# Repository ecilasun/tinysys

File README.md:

# tinysys

# What is it?

Tinysys started out as a hobby project. It now has two RISC-V cores, and several other facilities listed below, and can happily run most software with minimal tweaks.

Of course, before you ask, it does run DOOM, and with sound and keyboard input! (Lately, it has been running Quake as well.)

# System specifications

- 2x RISC-V based CPUs (architecture: rv32im_zicsr_zifencei_zfinx)
- First core runs the OS kernel and user processes
- Second core is reserved for user processes
- 175MHz bus and CPU clock, semi-pipelined execution
- Vectored or direct interrupt support
- Supports instruction fence and data cache flush/invalidate operations
- Single precision FPU per CPU (no float control CRSs)
- Float and integer GPRs share the same register space (zfinx extension)
- 32 GRPs x 32 bits
- 4096 CSRs x 32 bits (some registers reserved for CPU and some are immutable)
- All CPUs have access to each-other's CSR register files via memory mapped addresses
- Integer multiply / divide units per CPU
- Software, hardware and timer interrupts per CSR per core
- 16Kbytes of direct mapped instruction cache (256 lines x 64 bytes)
- 32Kbytes of direct mapped data cache (512 lines x 64 bytes)
- 128 bit AXI4 bus with 32 bit address line
- Memory arbiter for on-board device system memory access (round-robin)
- Memory mapped external hardware (audio / video etc)
- HDMI 1.4b compatible video and audio output via external chip (12 bits per pixel, 16bps stereo 44/22/11KHz for audio, RGB or paletted modes)
- SDCard for file I/O
- 4 debug LEDs (also shared by OS as indicators)
- Custom preemptive multitasking OS, with file I/O and basic memory allocator via syscalls
- Optionally, a rom.bin image can be loaded from SDCard to replace the OS in ROM
- ESP32S3 on board for I/O handling (UART serial connected directly for CLI and other future connectivity, running at 460800 baud)
- Future revisions will use USB-OTG on the ESP32S3 module to allow for mass storage access to the device
- 16Kbytes mailbox memory for task scheduler + general purpose use (uncached)
- 16Kbytes of scratchpad memory for inter-processor communications or temporary data storage (uncached)
- Horizontal blanking interrupts to synchronize CPU with VPU for video effects or interrupt driven vsync page flip

# Overview of the processing units

## CPU
Based on 32 bit RISC-V ISA. Implements base integer instruction set, required cache operations (I$ and D$) and a large CSR file.
The core currently has an average instruction retirement rate of ~6 CPI (clocks per instruction) and runs at 175MHz, which
is also the speed of the AXI4 bus, where all peripherals and memory reside.

### Fetch/Decode/IRQ
This unit reads an instruction at PC, decodes it and outputs it (together with its PC) to instruction output FIFO (IFIFO). If it's an interrupt entry/exit or some other special instruction (for instance I$ flush) then it is handled entirely within the fetch unit. This unit is also responsible for inserting pre/post interrupt code from an internal ROM at interrupt or exception time. Conditional branches will place fetch unit into an idle state, where it will wait for the execute unit to resolve the target branch address. This means there's no branch prediction on the CPU just yet.

### Execute/Load/Store
This unit will read an instruction from the IFIFO if available, load registers with values, execute (ALU/BLU/CSR/SYS) and decide on new branch target if there's a branch involved. After deciding on the branch address, fetch unit is notified so it can resume instruction fetches. Where possible, load or store operations will attempt to overlap with fetch and execution.

## VPU
Video processing unit. Handles scan-out of various video sizes (320x240 and 640x480) and bit depths (8bpp index color or 16bpp RGB color). It contains a scanline cache which is populated via burst reads from system memory, from which either a scan-doubled or single line is output to the display, based on video mode height. The device allows for mid-frame change of resolution via hblank interrupts.

## APU
Audio processing unit. Handles RAW audio outputs, and also manages 44/22/11KHz stereo playback and double-buffer handling of RAW audio.

# Overview of the bus

## AXI4 bus
The AXI4 bus, running at 175MHz, connects all of the processing units to memory or devices. In the case of memory, access is cached per perhipheral as needed. Memory mapped device access is always uncached.

# Contributors

```
Martin Hedlund

  tbm_vsnprintf() and tbm_printf() functions

Wade Brainerd

  fcvtswu4sat instruction
```

# Custom instructions

## Convert from float to 4 bit integer, saturated (FCVTSWU5SAT)

This instuction has been contributed by Wade Brainerd. It's very useful in converting floating point values to device specific 4 bit color values.

The following python script helps encode a hex representation of this instruction, for convenience:

```
op = 0b1010011		# OP-FP (floating point operation)
rd = 0b01010		# destination register - a0 in this sample (a0 == x10)
rs1 = 0b01011		# source register - a1 in this sample (a1 == x11)
funct7 = 0b1100001	# funct5 F7_FCVTSWU5SAT - this is our new sub-instruction
inst = op | (rd << 7) | (rs1 << 15) | (funct7 << 25)

print(f"{inst:x}")
```

You can then use it in code as follows:

```
inline uint32_t ftoui4sat(float value)
{
  uint32_t retval;
  asm (
    "mv a1, %1;"
    ".insn 0xc2058553;" // fcvtswu4sat a0, a1 // note A0==cpu.x10, A1==cpu.x11
    "mv %0, a0; "
    : "=r" (retval)
    : "r" (value)
    : "a0", "a1"
  );
  return retval;
}
```

P.S. For the future we might be able to do this natively on a RISC-V or propose an extension for arbitrary saturation for custom formats.

# Software

Please see [README.md](./software/README.md) for details on software samples, ROM and prerequisites for building ELF files.

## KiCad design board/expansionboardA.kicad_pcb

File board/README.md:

# expansionboardA

This repository contains KiCAD 7 project files for an expansion module built for QMTECH A7 200T core board.
Required libraries (models and symbols) are included with the project.

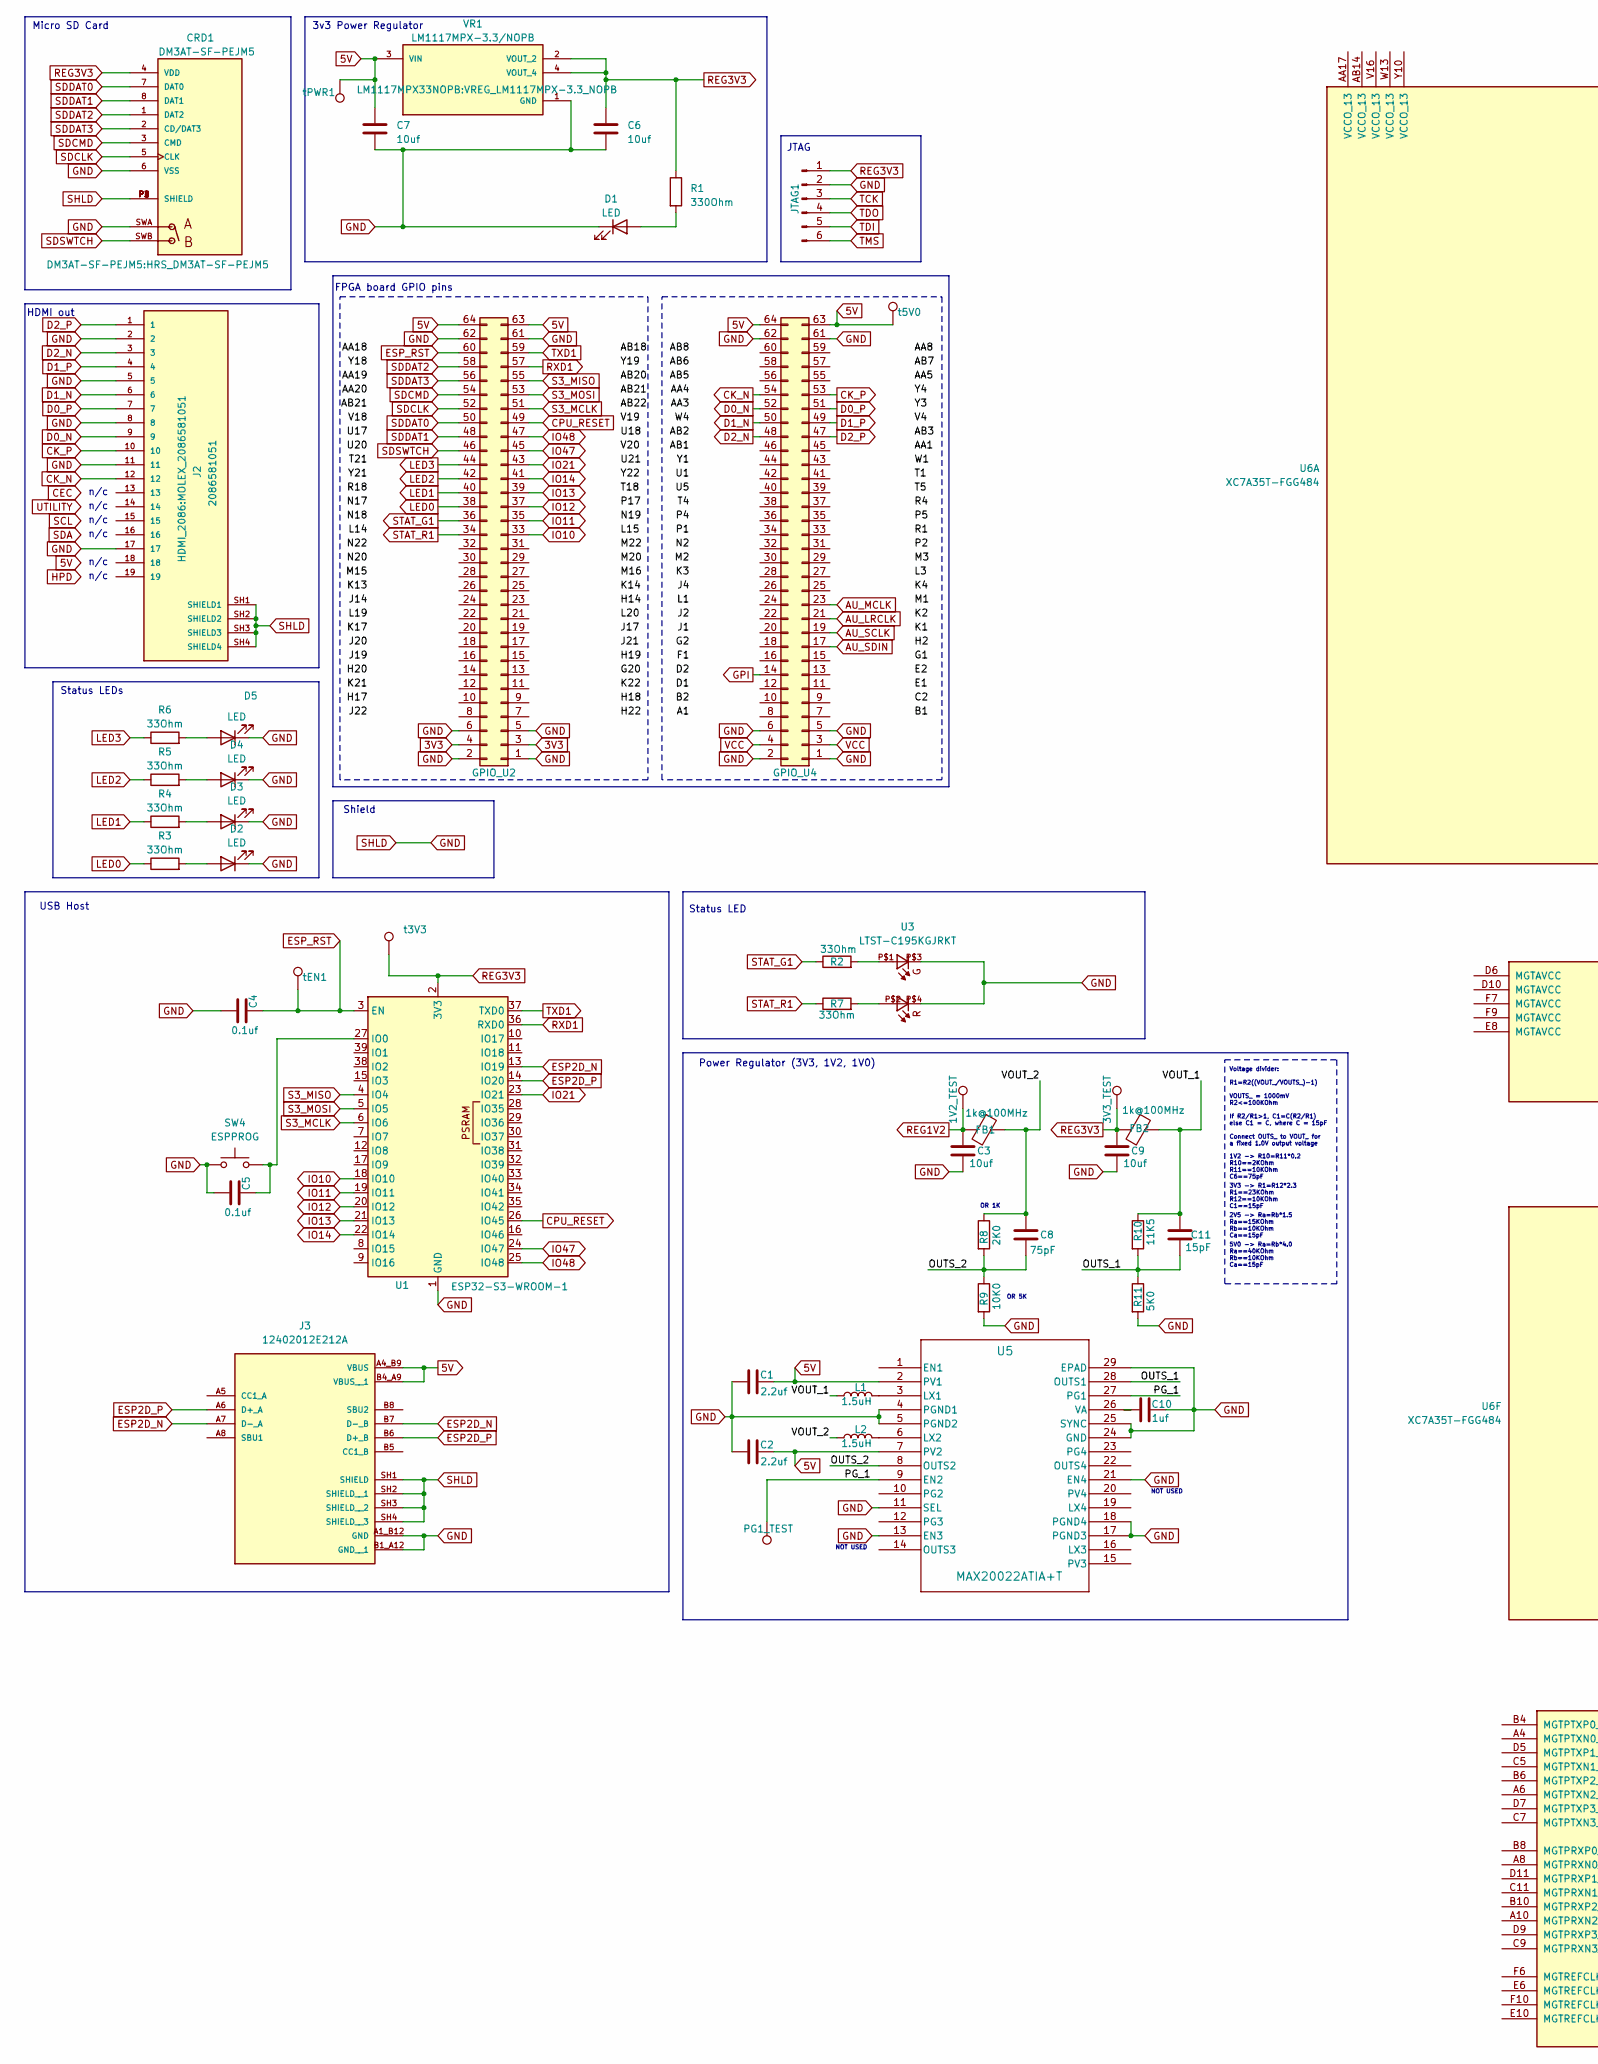
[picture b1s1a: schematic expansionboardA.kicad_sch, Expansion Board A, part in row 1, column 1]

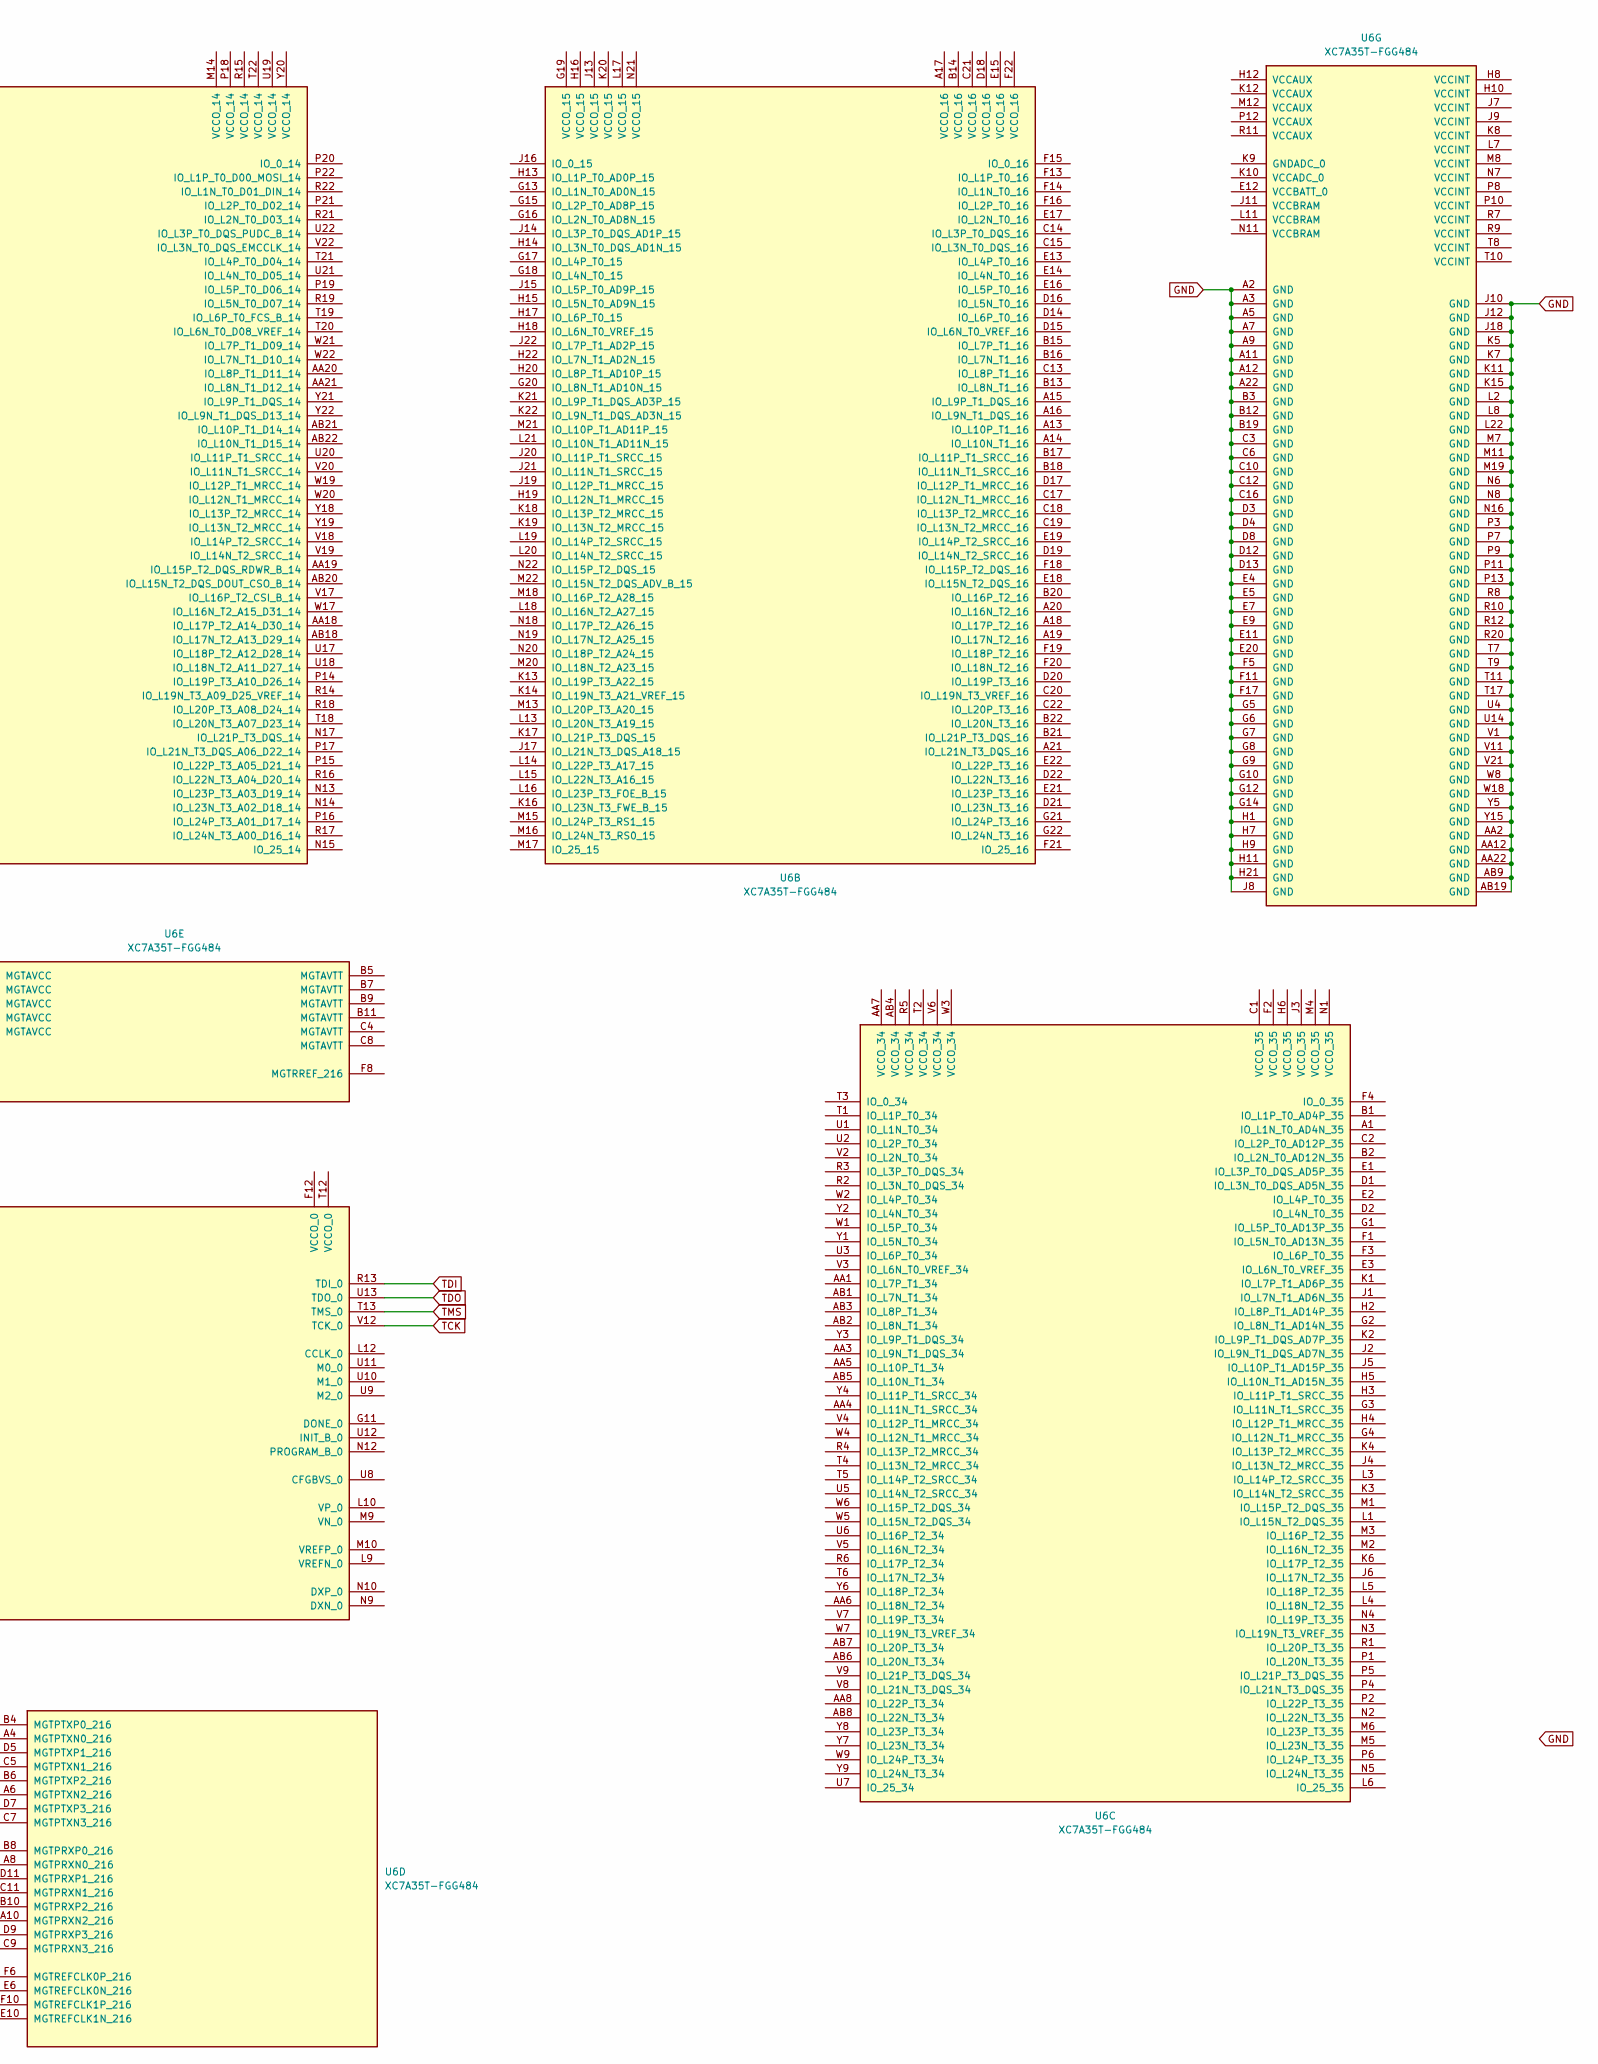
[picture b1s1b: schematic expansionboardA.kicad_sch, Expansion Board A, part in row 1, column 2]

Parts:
C1, C2: 2.2uf; C_0603_1608Metric_Pad1.08x0.95mm_HandSolder
C3, C9: 10uf; C_0603_1608Metric_Pad1.08x0.95mm_HandSolder
C4, C5: 0.1uf; C_0603_1608Metric_Pad1.08x0.95mm_HandSolder
C6, C7: 10uf; C_0805_2012Metric_Pad1.18x1.45mm_HandSolder
C8: 75pF; C_0603_1608Metric_Pad1.08x0.95mm_HandSolder
C10: 1uf; C_0603_1608Metric_Pad1.08x0.95mm_HandSolder
C11: 15pF; C_0603_1608Metric_Pad1.08x0.95mm_HandSolder
CRD1: DM3AT-SF-PEJM5; HRS_DM3AT-SF-PEJM5
D1, D2, D3, D4, D5: LED; LED_1206_3216Metric_Pad1.42x1.75mm_HandSolder
FB1, FB2: 1k@100MHz; R_0805_2012Metric_Pad1.20x1.40mm_HandSolder
J2: 2086581051; MOLEX_2086581051; PARTREV A
J3: 12402012E212A; AMPHENOL_12402012E212A; PARTREV 4
JTAG1: Conn_01x06_Pin; PinHeader_1x06_P2.54mm_Vertical
L1, L2: 1.5uH; L_0805_2012Metric
R1: 330Ohm; R_0603_1608Metric_Pad0.98x0.95mm_HandSolder
R2, R3, R4, R5, R6, R7: 33Ohm; R_0603_1608Metric_Pad0.98x0.95mm_HandSolder
R8: 2K0; R_0603_1608Metric_Pad0.98x0.95mm_HandSolder
R9: 10K0; R_0603_1608Metric_Pad0.98x0.95mm_HandSolder
R10: 11K5; R_0603_1608Metric_Pad0.98x0.95mm_HandSolder
R11: 5K0; R_0603_1608Metric_Pad0.98x0.95mm_HandSolder
SW4: ESPPROG; SW_Tactile_SPST_NO_Straight_CK_PTS636Sx25SMTRLFS
U1: ESP32-S3-WROOM-1
U2: GPIO_U2; PinSocket_2x32_P2.54mm_Vertical
U3: LTST-C195KGJRKT; LTST-BILED-15X16
U4: GPIO_U4; PinSocket_2x32_P2.54mm_Vertical
U5: MAX20022ATIA+T; 21-0140_T2855&plus_5_MXM-M
U6: XC7A35T-FGG484; Xilinx_FGG484
VR1: LM1117MPX-3.3/NOPB; VREG_LM1117MPX-3.3_NOPB; PARTREV O
t1V1: 1V2_TEST; TestPoint_Pad_1.0x1.0mm
t3V1: 3V3_TEST; TestPoint_Pad_1.0x1.0mm
t3V3, t5V0: TestPoint; TestPoint_Pad_D1.0mm
tEN1: TestPoint; TestPoint_Pad_D1.0mm
tPG1: PG1_TEST; TestPoint_Pad_1.0x1.0mm
tPWR1: TestPoint; TestPoint_Pad_D1.0mm

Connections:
3V3: U2.3, U2.4
5V: C1.2, C2.2, C7.1, J3.A4_B9 (VBUS), J3.B4_A9 (VBUS__1), U2.63, U2.64, U4.63, U4.64, U5.2 (PV1), U5.7 (PV2), VR1.3 (VIN), t5V0.1, tPWR1.1
/OUTS_1: C11.2, R10.2, R11.1, U5.28 (OUTS1)
/OUTS_2: C8.2, R8.2, R9.1, U5.8 (OUTS2)
/PG_1: U5.9 (EN2), U5.27 (PG1), tPG1.1
/VOUT_1: C11.1, FB2.1, L1.1, R10.1
/VOUT_2: C8.1, FB1.1, L2.1, R8.1
AU_LRCLK: U4.21
AU_MCLK: U4.23
AU_SCLK: U4.19
AU_SDIN: U4.17
CK_N: J2.12, U4.54
CK_P: J2.10, U4.53
CPU_RESET: U1.26 (IO45), U2.49
D0_N: J2.9, U4.52
D0_P: J2.7, U4.51
D1_N: J2.6, U4.50
D1_P: J2.4, U4.49
D2_N: J2.3, U4.48
D2_P: J2.1, U4.47
ESP2D_N: J3.A7 (D-_A), J3.B7 (D-_B), U1.13 (IO19)
ESP2D_P: J3.A6 (D+_A), J3.B6 (D+_B), U1.14 (IO20)
ESP_RST: C4.1, U1.3 (EN), U2.60, tEN1.1
GND: C1.1, C2.1, C3.2, C4.2, C5.2, C6.2, C7.2, C9.2, C10.2, CRD1.6 (VSS), CRD1.P1 (SHIELD), CRD1.P2 (SHIELD), CRD1.P3 (SHIELD), CRD1.P4 (SHIELD), CRD1.SWA, D1.1 (K), D2.1 (K), D3.1 (K), D4.1 (K), D5.1 (K), J2.2, J2.5, J2.8, J2.11, J2.17, J2.SH1 (SHIELD1), J2.SH2 (SHIELD2), J2.SH3 (SHIELD3), J2.SH4 (SHIELD4), J3.A1_B12 (GND), J3.B1_A12 (GND__1), J3.SH1 (SHIELD), J3.SH2 (SHIELD__1), J3.SH3 (SHIELD__2), J3.SH4 (SHIELD__3), JTAG1.2, R9.2, R11.2, SW4.1, U1.1 (GND), U1.40 (GND), U1.41 (GND), U2.1, U2.2, U2.5, U2.6, U2.61, U2.62, U3.P$3, U3.P$4, U4.1, U4.2, U4.5, U4.6, U4.61, U4.62, U5.4 (PGND1), U5.5 (PGND2), U5.11 (SEL), U5.13 (EN3), U5.17 (PGND3), U5.18 (PGND4), U5.21 (EN4), U5.24 (GND), U5.25 (SYNC), U5.29 (EPAD), U6.A2 (GND), U6.A3 (GND), U6.A5 (GND), U6.A7 (GND), U6.A9 (GND), U6.A11 (GND), U6.A12 (GND), U6.A22 (GND), U6.AA2 (GND), U6.AA12 (GND), U6.AA22 (GND), U6.AB9 (GND), U6.AB19 (GND), U6.B3 (GND), U6.B12 (GND), U6.B19 (GND), U6.C3 (GND), U6.C6 (GND), U6.C10 (GND), U6.C12 (GND), U6.C16 (GND), U6.D3 (GND), U6.D4 (GND), U6.D8 (GND), U6.D12 (GND), U6.D13 (GND), U6.E4 (GND), U6.E5 (GND), U6.E7 (GND), U6.E9 (GND), U6.E11 (GND), U6.E20 (GND), U6.F5 (GND), U6.F11 (GND), U6.F17 (GND), U6.G5 (GND), U6.G6 (GND), U6.G7 (GND), U6.G8 (GND), U6.G9 (GND), U6.G10 (GND), U6.G12 (GND), U6.G14 (GND), U6.H1 (GND), U6.H7 (GND), U6.H9 (GND), U6.H11 (GND), U6.H21 (GND), U6.J8 (GND), U6.J10 (GND), U6.J12 (GND), U6.J18 (GND), U6.K5 (GND), U6.K7 (GND), U6.K11 (GND), U6.K15 (GND), U6.L2 (GND), U6.L8 (GND)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
GPI: U4.14
IO10: U1.18 (IO10), U2.33
IO11: U1.19 (IO11), U2.35
IO12: U1.20 (IO12), U2.37
IO13: U1.21 (IO13), U2.39
IO14: U1.22 (IO14), U2.41
IO21: U1.23 (IO21), U2.43
IO47: U1.24 (IO47), U2.45
IO48: U1.25 (IO48), U2.47
LED0: R3.1, U2.38
LED1: R4.1, U2.40
LED2: R5.1, U2.42
LED3: R6.1, U2.44
unnamed: D1.2 (A), R1.2
unnamed: D2.2 (A), R3.2
unnamed: D3.2 (A), R4.2
unnamed: D4.2 (A), R5.2
unnamed: D5.2 (A), R6.2
unnamed: R2.2, U3.P$1
unnamed: R7.2, U3.P$2
unnamed: C5.1, SW4.2, U1.27 (IO0)
unnamed: L1.2, U5.3 (LX1)
unnamed: L2.2, U5.6 (LX2)
unnamed: C10.1, U5.26 (VA)
REG1V2: C3.1, FB1.2, t1V1.1
REG3V3: C6.1, C9.1, CRD1.4 (VDD), FB2.2, JTAG1.1, R1.1, U1.2 (3V3), VR1.2 (VOUT_2), VR1.4 (VOUT_4), t3V1.1, t3V3.1
RXD1: U1.36 (RXD0), U2.57
S3_MCLK: U1.6 (IO6), U2.51
S3_MISO: U1.4 (IO4), U2.55
S3_MOSI: U1.5 (IO5), U2.53
SDCLK: CRD1.5 (CLK), U2.52
SDCMD: CRD1.3 (CMD), U2.54
SDDAT0: CRD1.7 (DAT0), U2.50
SDDAT1: CRD1.8 (DAT1), U2.48
SDDAT2: CRD1.1 (DAT2), U2.58
SDDAT3: CRD1.2 (CD/DAT3), U2.56
SDSWTCH: CRD1.SWB, U2.46
STAT_G1: R2.1, U2.36
STAT_R1: R7.1, U2.34
TCK: JTAG1.3, U6.V12 (TCK_0)
TDI: JTAG1.5, U6.R13 (TDI_0)
TDO: JTAG1.4, U6.U13 (TDO_0)
TMS: JTAG1.6, U6.T13 (TMS_0)
TXD1: U1.37 (TXD0), U2.59
VCC: U4.3, U4.4

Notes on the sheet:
NOT USED
OR 1K
2V5 -> Ra=Rb*1.5 Ra==15KOhm Rb==10KOhm Ca==15pF
n/c
FPGA board GPIO pins
5V0 -> Ra=Rb*4.0 Ra==40KOhm Rb==10KOhm Ca==15pF
Micro SD Card
JTAG
Status LED
Power Regulator (3V3, 1V2, 1V0)
Status LEDs
USB Host
Shield
Voltage divider: R1=R2((VOUT_/VOUTS_)−1) VOUTS_ = 1000mV R2<=100KOhm If R2/R1>1, C1=C(R2/R1) else C1 = C, where C = 15pF Connect OUTS_ to VOUT_ for a fixed 1.0V output voltage
1V2 -> R10=R11*0.2 R10==2KOhm R11==10KOhm C6==75pF
3v3 Power Regulator
HDMI out
3V3 -> R1=R12*2.3 R1==23KOhm R12==10KOhm C1==15pF
OR 5K

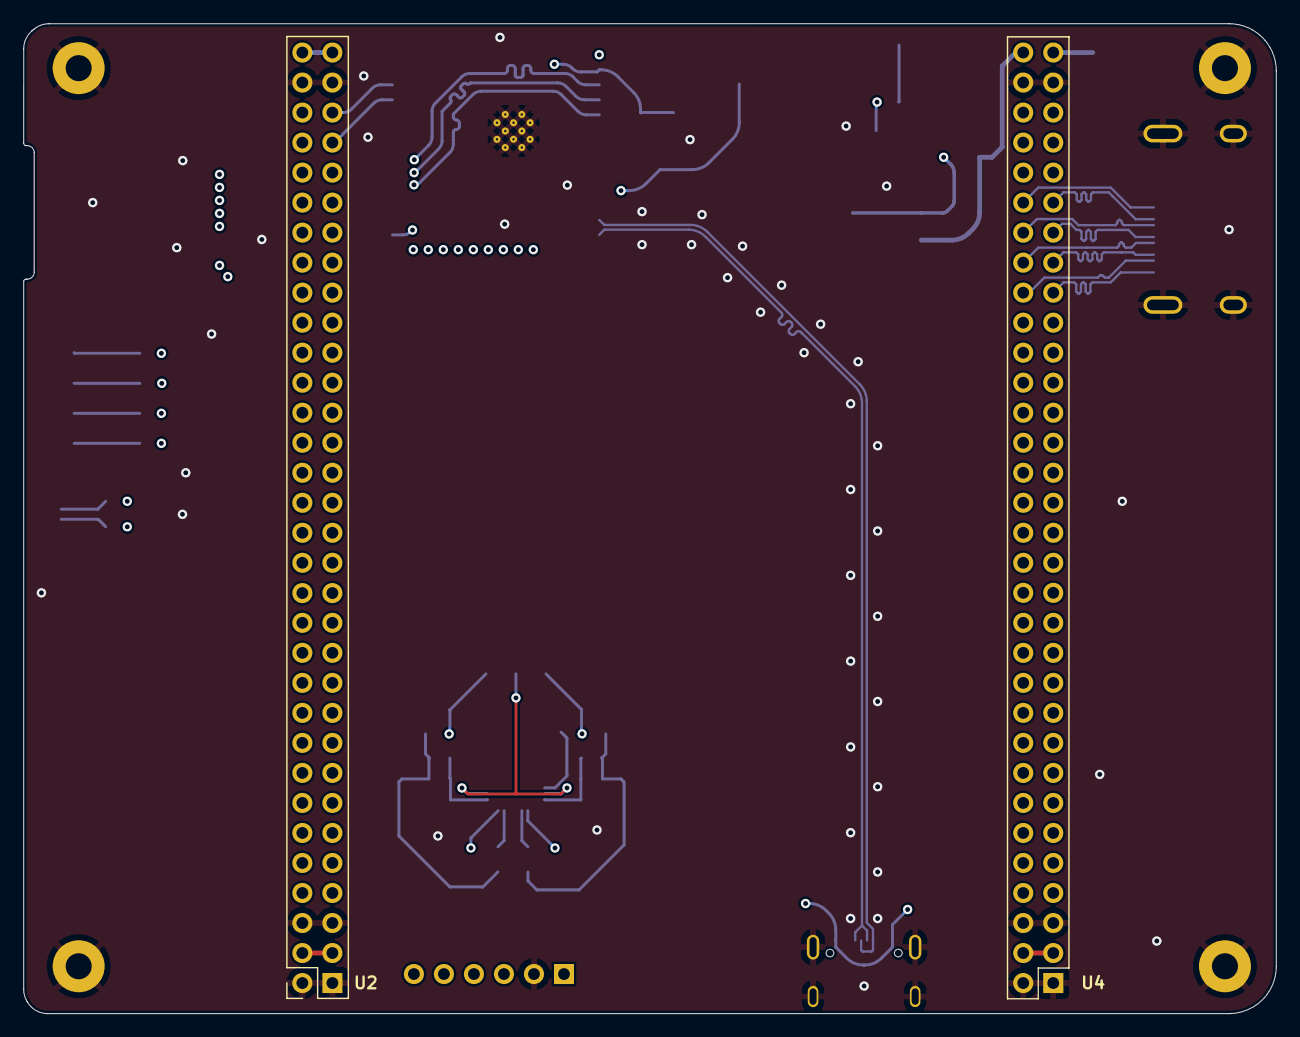
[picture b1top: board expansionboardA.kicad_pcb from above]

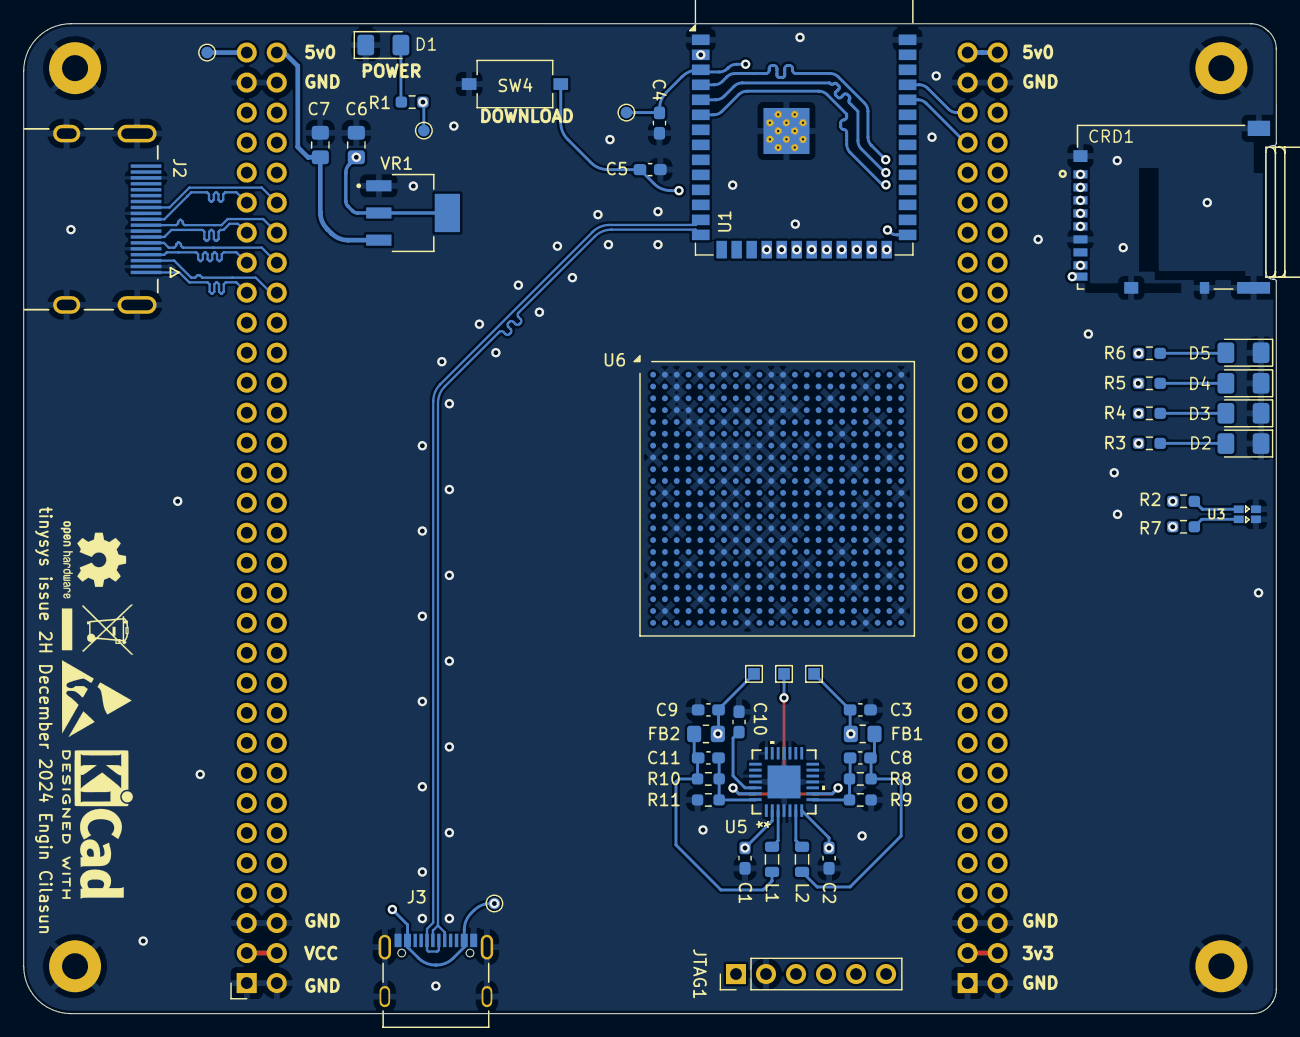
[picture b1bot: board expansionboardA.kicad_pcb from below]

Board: 4 copper layers, 106.0 x 83.8 mm, 50 parts (50 on the bottom side), 64 nets.

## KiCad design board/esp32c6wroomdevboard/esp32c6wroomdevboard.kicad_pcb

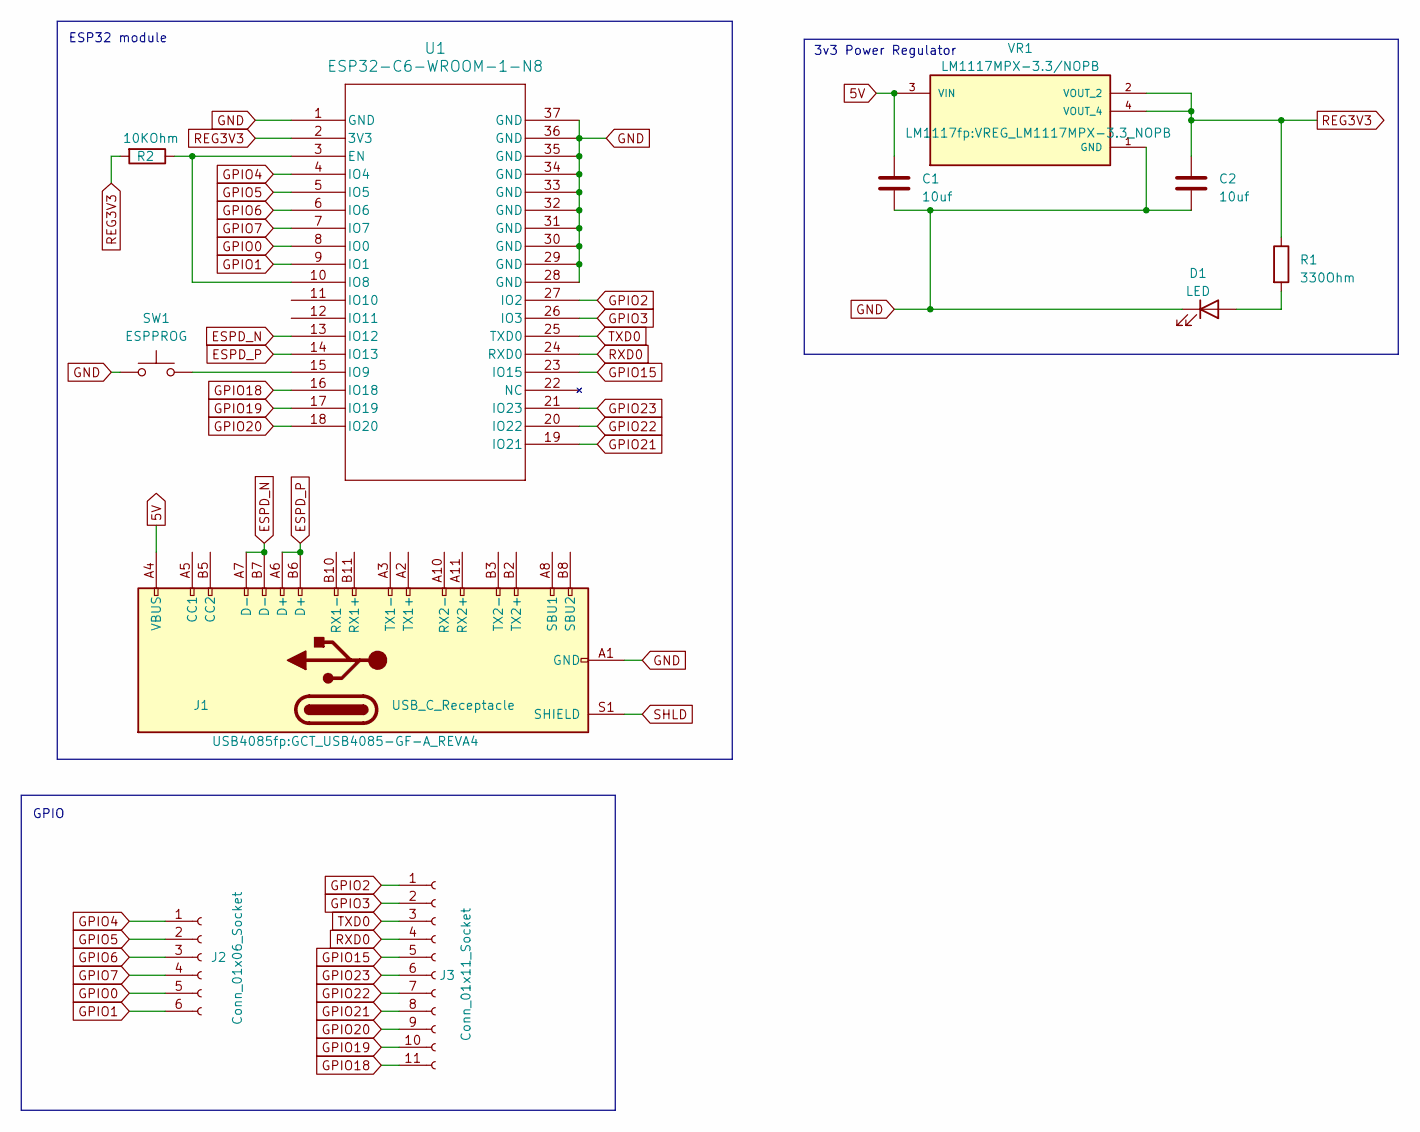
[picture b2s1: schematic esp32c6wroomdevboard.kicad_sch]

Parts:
C1, C2: 10uf; C_0805_2012Metric_Pad1.18x1.45mm_HandSolder
D1: LED; LED_1206_3216Metric_Pad1.42x1.75mm_HandSolder
J1: USB_C_Receptacle; GCT_USB4085-GF-A_REVA4
J2: Conn_01x06_Socket; PinHeader_1x06_P2.54mm_Vertical
J3: Conn_01x11_Socket; PinHeader_1x11_P2.54mm_Vertical
R1: 330Ohm; R_0603_1608Metric_Pad0.98x0.95mm_HandSolder
R2: 10KOhm; R_0603_1608Metric_Pad0.98x0.95mm_HandSolder
SW1: ESPPROG; SW_Tactile_SPST_NO_Straight_CK_PTS636Sx25SMTRLFS
U1: ESP32-C6-WROOM-1-N8; MOD28_ESP32-C6-WROOM-1_EXP
VR1: LM1117MPX-3.3/NOPB; VREG_LM1117MPX-3.3_NOPB; PARTREV O

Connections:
5V: C1.1, J1.A4 (VBUS), J1.A9 (VBUS), J1.B4 (VBUS), J1.B9 (VBUS), VR1.3 (VIN)
ESPD_N: J1.A7 (D-), J1.B7 (D-), U1.13 (IO12)
ESPD_P: J1.A6 (D+), J1.B6 (D+), U1.14 (IO13)
GND: C1.2, C2.2, D1.1 (K), J1.A1 (GND), J1.A12 (GND), J1.B1 (GND), J1.B12 (GND), SW1.1, U1.1 (GND), U1.28 (GND), U1.29 (GND), U1.30 (GND), U1.31 (GND), U1.32 (GND), U1.33 (GND), U1.34 (GND), U1.35 (GND), U1.36 (GND), U1.37 (GND), VR1.1 (GND)
GPIO0: J2.5, U1.8 (IO0)
GPIO1: J2.6, U1.9 (IO1)
GPIO2: J3.1, U1.27 (IO2)
GPIO3: J3.2, U1.26 (IO3)
GPIO4: J2.1, U1.4 (IO4)
GPIO5: J2.2, U1.5 (IO5)
GPIO6: J2.3, U1.6 (IO6)
GPIO7: J2.4, U1.7 (IO7)
GPIO15: J3.5, U1.23 (IO15)
GPIO18: J3.11, U1.16 (IO18)
GPIO19: J3.10, U1.17 (IO19)
GPIO20: J3.9, U1.18 (IO20)
GPIO21: J3.8, U1.19 (IO21)
GPIO22: J3.7, U1.20 (IO22)
GPIO23: J3.6, U1.21 (IO23)
unnamed: D1.2 (A), R1.2
unnamed: R2.1, U1.3 (EN), U1.10 (IO8)
unnamed: SW1.2, U1.15 (IO9)
REG3V3: C2.1, R1.1, R2.2, U1.2 (3V3), VR1.2 (VOUT_2), VR1.4 (VOUT_4)
RXD0: J3.4, U1.24 (RXD0)
SHLD: J1.S1 (SHIELD)
TXD0: J3.3, U1.25 (TXD0)

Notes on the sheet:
3v3 Power Regulator
GPIO
ESP32 module

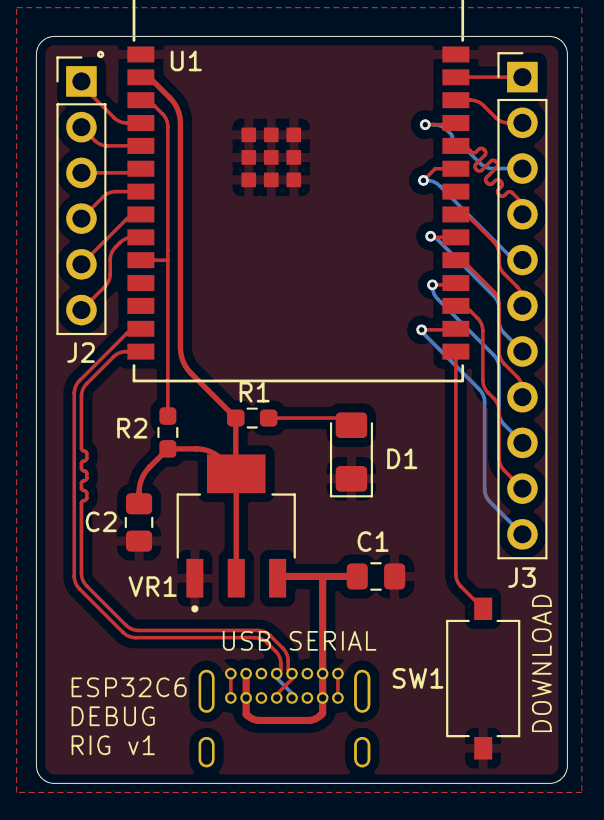
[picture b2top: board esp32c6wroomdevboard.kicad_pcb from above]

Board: 2 copper layers, 29.5 x 41.5 mm, 11 parts (1 on the bottom side), 25 nets.

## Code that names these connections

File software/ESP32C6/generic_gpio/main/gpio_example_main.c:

/* GPIO Example

   This example code is in the Public Domain (or CC0 licensed, at your option.)

   Unless required by applicable law or agreed to in writing, this
   software is distributed on an "AS IS" BASIS, WITHOUT WARRANTIES OR
   CONDITIONS OF ANY KIND, either express or implied.
*/
#include <stdio.h>
#include <string.h>
#include <stdlib.h>
#include <inttypes.h>
#include "freertos/FreeRTOS.h"
#include "freertos/task.h"
#include "freertos/queue.h"
#include "driver/gpio.h"

/**
 * Brief:
 * This test code shows how to configure gpio and how to use gpio interrupt.
 *
 * GPIO status:
 * GPIO18: output (ESP32C2/ESP32H2 uses GPIO8 as the second output pin)
 * GPIO19: output (ESP32C2/ESP32H2 uses GPIO9 as the second output pin)
 * GPIO4:  input, pulled up, interrupt from rising edge and falling edge
 * GPIO5:  input, pulled up, interrupt from rising edge.
 *
 * Note. These are the default GPIO pins to be used in the example. You can
 * change IO pins in menuconfig.
 *
 * Test:
 * Connect GPIO18(8) with GPIO4
 * Connect GPIO19(9) with GPIO5
 * Generate pulses on GPIO18(8)/19(9), that triggers interrupt on GPIO4/5
 *
 */

#define GPIO_OUTPUT_IO_0    CONFIG_GPIO_OUTPUT_0
#define GPIO_OUTPUT_IO_1    CONFIG_GPIO_OUTPUT_1
#define GPIO_OUTPUT_PIN_SEL  ((1ULL<<GPIO_OUTPUT_IO_0) | (1ULL<<GPIO_OUTPUT_IO_1))
/*
 * Let's say, GPIO_OUTPUT_IO_0=18, GPIO_OUTPUT_IO_1=19
 * In binary representation,
 * 1ULL<<GPIO_OUTPUT_IO_0 is equal to 0000000000000000000001000000000000000000 and
 * 1ULL<<GPIO_OUTPUT_IO_1 is equal to 0000000000000000000010000000000000000000
 * GPIO_OUTPUT_PIN_SEL                0000000000000000000011000000000000000000
 * */
#define GPIO_INPUT_IO_0     CONFIG_GPIO_INPUT_0
#define GPIO_INPUT_IO_1     CONFIG_GPIO_INPUT_1
#define GPIO_INPUT_PIN_SEL  ((1ULL<<GPIO_INPUT_IO_0) | (1ULL<<GPIO_INPUT_IO_1))
/*
 * Let's say, GPIO_INPUT_IO_0=4, GPIO_INPUT_IO_1=5
 * In binary representation,
 * 1ULL<<GPIO_INPUT_IO_0 is equal to 0000000000000000000000000000000000010000 and
 * 1ULL<<GPIO_INPUT_IO_1 is equal to 0000000000000000000000000000000000100000
 * GPIO_INPUT_PIN_SEL                0000000000000000000000000000000000110000
 * */
#define ESP_INTR_FLAG_DEFAULT 0

static QueueHandle_t gpio_evt_queue = NULL;

static void IRAM_ATTR gpio_isr_handler(void* arg)
{
    uint32_t gpio_num = (uint32_t) arg;
    xQueueSendFromISR(gpio_evt_queue, &gpio_num, NULL);
}

static void gpio_task_example(void* arg)
{
    uint32_t io_num;
    for (;;) {
        if (xQueueReceive(gpio_evt_queue, &io_num, portMAX_DELAY)) {
            printf("GPIO[%"PRIu32"] intr, val: %d\n", io_num, gpio_get_level(io_num));
        }
    }
}

void app_main(void)
{
    //zero-initialize the config structure.
    gpio_config_t io_conf = {};
    //disable interrupt
    io_conf.intr_type = GPIO_INTR_DISABLE;
    //set as output mode
    io_conf.mode = GPIO_MODE_OUTPUT;
    //bit mask of the pins that you want to set,e.g.GPIO18/19
    io_conf.pin_bit_mask = GPIO_OUTPUT_PIN_SEL;
    //disable pull-down mode
    io_conf.pull_down_en = 0;
    //disable pull-up mode
    io_conf.pull_up_en = 0;
    //configure GPIO with the given settings
    gpio_config(&io_conf);

    //interrupt of rising edge
    io_conf.intr_type = GPIO_INTR_ANYEDGE;
    //bit mask of the pins, use GPIO4/5 here
    io_conf.pin_bit_mask = GPIO_INPUT_PIN_SEL;
    //set as input mode
    io_conf.mode = GPIO_MODE_INPUT;
    //enable pull-up mode
    io_conf.pull_up_en = 1;
    gpio_config(&io_conf);

    //create a queue to handle gpio event from isr
    gpio_evt_queue = xQueueCreate(10, sizeof(uint32_t));
    //start gpio task
    xTaskCreate(gpio_task_example, "gpio_task_example", 2048, NULL, 10, NULL);

    //install gpio isr service
    gpio_install_isr_service(ESP_INTR_FLAG_DEFAULT);
    //hook isr handler for specific gpio pin
    gpio_isr_handler_add(GPIO_INPUT_IO_0, gpio_isr_handler, (void*) GPIO_INPUT_IO_0);
    //hook isr handler for specific gpio pin
    gpio_isr_handler_add(GPIO_INPUT_IO_1, gpio_isr_handler, (void*) GPIO_INPUT_IO_1);

    //remove isr handler for gpio number.
    gpio_isr_handler_remove(GPIO_INPUT_IO_0);
    //hook isr handler for specific gpio pin again
    gpio_isr_handler_add(GPIO_INPUT_IO_0, gpio_isr_handler, (void*) GPIO_INPUT_IO_0);

    int cnt = 0;
    while (1) {
        printf("cnt: %d\n", cnt++);
        vTaskDelay(1000 / portTICK_PERIOD_MS);
		// Test output
        gpio_set_level(GPIO_OUTPUT_IO_0, cnt % 2);
        gpio_set_level(GPIO_OUTPUT_IO_1, cnt % 2);
    }
}

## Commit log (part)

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2024-11-23 Updated riscvtool build Updated documentation Updated some build script with correct riscvtool path Added prebuilt riscvtool.exe for Windows
2024-11-23 Added prebuilt riscvtool for Linux
2024-11-23 Updated riscvtool
2024-11-23 Updated executable state for risvtool
2024-11-24 update tinyremote
2024-11-24 Updated gateware
2024-11-25 Stack overlap and task fixes
2024-11-25 Updated ROM
2024-11-26 task add moved to syscall
2024-11-28 Updates to task, utilities and ROM
2024-11-29 Added quake port
2024-11-29 Fixed my git source
2024-11-29 some emulator work updated quake binary and makefile
2024-11-30 Updates to shrink rom a little bit
2024-11-30 Dropped back to 2 cores not to exceed thermal limits Updated emulator / ROM / SDK and samples Removed access to XADC unit Removed imgui + sample Removed ADC sample
2024-12-01 Board updates for version 2G Factory test ROM update
2024-12-08 moved tinyprint/scan code to SDK, out of ROM code updated dump / memtest / more / recv / usbinfo Updated ROM Bumped sdcard / usb SPI to 100MHz base (25MHz clock)
2024-12-08 Updated quake
2024-12-08 minor fix
2024-12-09 Safer reboot with both fetch and control tied to cpuresetreq
2024-12-09 WNS fix ESP32 ROM image fix
2024-12-09 File upload code reworked Added LZ4 compression
2024-12-10 Some task system revisions
2024-12-10 Removed mandeltask sample
2024-12-11 Updated reset startup in CLI task
2024-12-11 Update to board project
2024-12-12 Working on startup code Working on task exit
2024-12-12 More asm / ROM changes
2024-12-12 maybe a fix
2024-12-13 minor code updates and comments removed async resets cpuresetreq is an actual hardware reset now placed missing IR reset updated ROM updated Vivado project
2024-12-14 Added missing reset lines Some syntax and typo fixes in OS code Updated ROM
2024-12-14 Bumped UART speed to 460800 baud
2024-12-14 Updated ROM for emulator
2024-12-14 Minor emulator reset fix
2024-12-17 gained back bidirectional comm
2024-12-18 updated riscvtool added terminal mode to riscvtool added missing rx/tx resetn signal
2024-12-18 Added ESC to send CTRL+C and console echo back to riscvtool
2024-12-18 Updated gateware, removed redundant files
2024-12-19 Updated windows riscvtool binary
2024-12-19 Reorder init sequence for linux
2024-12-19 minor update to esp firmware
2024-12-19 Updated hblank sample
2024-12-19 GDB stub WiP
2024-12-19 Added debug notes
2024-12-19 more responses added to gdb stub using temp ram region for uart print
2024-12-20 added thread xml info
2024-12-20 some data byte order fixes
2024-12-20 added hex support to miniscanf updated debug stub
2024-12-20 default to led.elf sample for vscode gdb test
2024-12-20 Startup delay for ESP32
2024-12-20 More delay at startup
2024-12-20 more stub work
2024-12-24 Updated emulator GDB connection
2024-12-24 Started work on new board Added some new device documents Disabled in-ROM GDB to do the initial pass on emulator GDB-stub Updated ROM
2024-12-25 Fix to stub binary decoder
2024-12-25 Primitive debug register access
2024-12-25 some more gdb stub work for emulator
2024-12-27 Updated new board
2024-12-29 Updates to board files
2024-12-30 minor repairs to boot time
2024-12-30 Have to re-think GDB, removed stub for now
2024-12-31 Board update
2024-12-31 New board updates
2024-12-31 More board updates
2024-12-31 Removed stale samples
2024-12-31 Updated emulator and sdcard image
2025-01-01 Resistor mistake
2025-01-02 Board updates
2025-01-02 Updates to build tinyremote on Linux
2025-01-02 Compiled riscvtool on Linux instead of MacOS
2025-01-02 ROM Version report tidy up
2025-01-03 smaller ELF binaries some ROM updates
2025-01-03 dump and more now echo to local terminal
2025-01-03 Comment fix in readme
2025-01-04 Added support for scancode input from tinyremote
2025-01-04 Fixed an issue with modifier states in keyboard packets
2025-01-04 Updates to emulator side
2025-01-04 ROM keyboard code now interprets CTRL+C
2025-01-04 Simplified SDK uart key code handling Moved CTRL+C/~ handling to tinyremote
2025-01-04 Updated some notes
2025-01-05 fix for riscvtool file path compilcation
2025-01-05 removed accidentally distributed files
2025-01-05 added wad files to gitignore
2025-01-08 Joystick fixes, doom WiP
2025-01-08 fix one byte accidental shift
2025-01-08 Updated keys sample to read joystick as well
2025-01-09 Little bit hacky but tinryremote now has audio over line in
2025-01-09 updates to mac side
2025-01-10 Added prebuilt binaries for emulator and remote
2025-01-10 Fix boot setup for remote
2025-01-10 updated remote
2025-01-11 window resize fixes
2025-01-11 Fix memory leak
2025-01-11 linux tiny up
2025-01-16 Started to get rid of the video and audio chips and circuitry
2025-01-18 Board updates HDMI unit updates Removed redundant files Removed redundant constraints
2025-01-18 Updated emulator sdcard image
2025-01-18 Fixed color order of tinyrt
2025-01-18 Fixed timing (back to 150MHz)
2025-01-18 Auto-connect on UART loss Audio capture lag fix attempts
2025-01-19 More updates towards DMA fix
2025-01-20 Removed DMA unit due to timing complications Removed DMA usage and samples
2025-01-20 More DMA referrals removed
2025-01-20 Updated the ROM image and gateware
2025-01-21 Latest gateware
2025-01-21 Fixed some comments in specs
2025-01-21 one more comment
2025-01-26 Added automatic port detection for COM / tty to tinyremote
2025-01-27 Added SMD usb connector to library
2025-01-27 Board B reshaped
2025-02-02 out of bounds fix
2025-02-02 device report minor fix
2025-02-03 Updated binaries
2025-02-03 Attempting to fix timing closure once more
2025-02-04 Timing closure fixed properly this time Updated ROM Updated SDK Updated hblank sample Updated hblank interrupt hardware Removed redundant resets
2025-02-05 Updated tinyremote to work with more capture devices (resolution fix)
2025-02-05 More options added to ini file
2025-02-06 Small mistake in ini reporting
2025-02-08 Bugfix for audio playback device enumeration
2025-02-08 Fix for simulation
2025-02-11 Updated link to toolchain
2025-02-11 Minor fix to wording
2025-02-11 Updated emulator sdcard contents
2025-02-11 Revert "Updated emulator samples"
    This reverts commit b5f57141ca1635c609f5a752fa754637d936ceb6.
2025-02-13 Added bill of materials
2025-02-17 Some unimportant code cleanup
2025-02-17 more ignore fixes
2025-02-28 Mini typo fix
2025-02-28 Starting to add gdb debugger support
2025-03-01 Fixed signed/unsigned integer to float conversion bug
2025-03-01 Fixed scancode key entry
2025-03-01 Added support for joysticks
2025-03-01 More work on GDB
2025-03-01 work on breakpoints
2025-03-01 fixed memory response being 1 byte too short
2025-03-01 Added vscode debug template for mandelbrot Updated stub
2025-03-01 More breakpoint work
2025-03-02 Fix accidental debug option
2025-03-02 Accidentally checked in debug version
2025-03-03 minor emulator fixes
2025-03-03 Slightly better step but still not there
2025-03-03 Fix hang on exit if debugger was never attached
2025-03-03 removed gdb stub log messages by default
2025-03-05 missing config from debug launch.json
2025-03-05 Some task related fixes Updated ROM for emulator Rebuilt emulator Rebuilt riscvtool
2025-03-08 Temporary fix
2025-03-08 indentation fix
2025-03-08 Updated mod player vumeter to use tasks
2025-03-08 One more typo
2025-03-08 Minor emulator fix
2025-03-08 Missed a few video modes
2025-03-08 Small update to player
2025-03-09 Fix tinyremote launch folder during debugging
2025-03-09 More changes to mod player and rebuilt tinyremote
2025-03-09 Audio format fix for capture
2025-03-12 Emulator gdb shenanigans
2025-03-12 Big revamp of input handling
2025-03-12 Fixed quake
2025-03-14 fix macos build
2025-03-15 Rebuilt samples
2025-03-15 Additional music to test
2025-03-15 Headphones vs speakers
2025-03-15 Critical file upload fix
2025-03-15 Updates to capture code
2025-03-16 More cleanup
2025-03-16 Should not have checked in
2025-03-16 Makefiles updated with dump command
2025-03-16 -fno-delete-null-pointer-checks for quake
2025-03-17 Updated task switch code to also cope with PAUSED state
2025-03-17 Slightly more optimial emulator
2025-03-21 small fixes for unused code paths
2025-03-21 fixed mac builds updated macos emulator binary
2025-03-22 Added MJPG support to capture
2025-03-23 Added missing vectored interrupt support to emulator (unused)
2025-03-23 more vectored fixes
2025-03-23 two hearts
2025-03-25 Reset logic changed to reboot entire FPGA ROM updates
2025-03-25 Task stacks bumped to 16K Fixed gettimeofday syscall Fixed missing register from FPGA reset Updated ROM + gateware
2025-03-27 Added sdcard switch emulation and file watcher to emulator Renamed sample from starthere to hellodebugger
2025-03-28 fix macos/linux build of riscvtool rebuilt ROM slightly smaller
2025-03-28 Task memory reduced a small amount Task name is no longer copied to task memory
2025-03-28 Fixes
2025-03-28 ROM now echoes any important messages to UART
2025-03-28 Fix build
2025-03-29 Scratchpad memory is now 64K Reset is now more robust ROM updated
2025-03-29 Minor repairs for Linux build
2025-03-29 Fix for linux access issues to GL context on a timer callback
2025-03-29 Bumped scratchpad to 64K
2025-03-30 Major OS task system related changes
2025-03-30 Support Resizing Emulator (#15)
    With this change, you can resize the emulator window and the image stretches. It's not always pretty, but it does always work.
    To handle resizing, we don't even need to respond to the window resize events. We only need to:
    1. Tell SDL to make the window resizable
    2. Use the correct Surface once it's been resized.
    3. When copying from the composite surface to the window surface, we need to use `SDL_BlitScaled` over `SDL_BlitSurface`, which handles resizing.
    While debugging it, I realized the `SDL_Surface` is being held onto too long, _and_ the SDL docs explicitly call it out as "do not free" [here](https://wiki.libsdl.org/SDL2/SDL_GetWindowSurface):
2025-03-30 Fixed leaking SDL surface. FIxed leaking decoded blocks due to looking up map with wrong key. (#16)
2025-03-30 Updated linux binary for emulator
2025-03-30 Fixed memory leaks when refreshing emulator sdcard filesystem.
2025-03-31 Moved hardware files to own folder
2025-03-31 Add Various Missing Deletes
    Several places in the code were missing delete logic which were
    identified while investigating an unrelated memory leak.
2025-03-31 Frame pacing fix for linux
2025-03-31 Remove Incorrect CSR Mem Reset
    There's a reset for a CSRMem at index 2 but the bus only allocates 2
    CSRMem pointers so the third one (at index 2) is invalid.
    Thanks to Chris--B for finding this with UBSan.
2025-03-31 Small Memory Leak Fixes & Fix VS Project Paths (#18)
    * Fix Emulator VS Project Include Paths
    The previous paths were hardcoded to local directories which prevented
    the solution from compiling properly on other machines.
    This change updates the paths to use VS path macros instead which makes
    the include paths relative to the project directory.
    * Fix Small Memory Leak in RV32 Emulator
2025-03-31 Updated linux emulator binary
2025-03-31 Updates to mac build, checking in prebuilt emulator
2025-03-31 updating linux build run path
2025-04-03 Memory range safety and a minor optimization
2025-04-03 fixed task stack sizes
2025-04-03 rebuilt mac emulator
2025-04-05 bus acq
2025-04-05 Missing enum
2025-04-05 More missing defines
2025-04-05 Updated linux binary
2025-04-05 Updated macos binary
2025-04-05 Fix a fatal error
2025-04-05 Adde multithreaded emulator binary for windows
2025-04-07 Some ELF loader memory stomp fixes coming from the FAT32 library Updated ROMs Updated gateware
2025-04-07 updates macos binary
